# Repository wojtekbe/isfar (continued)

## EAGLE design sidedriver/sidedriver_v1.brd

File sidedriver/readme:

Motor1
M1-PWM -> PA1 -> TIM2_CH2

Tank
M2-PWM -> 

Ledd
SRV1
SRV2
LED-PWM

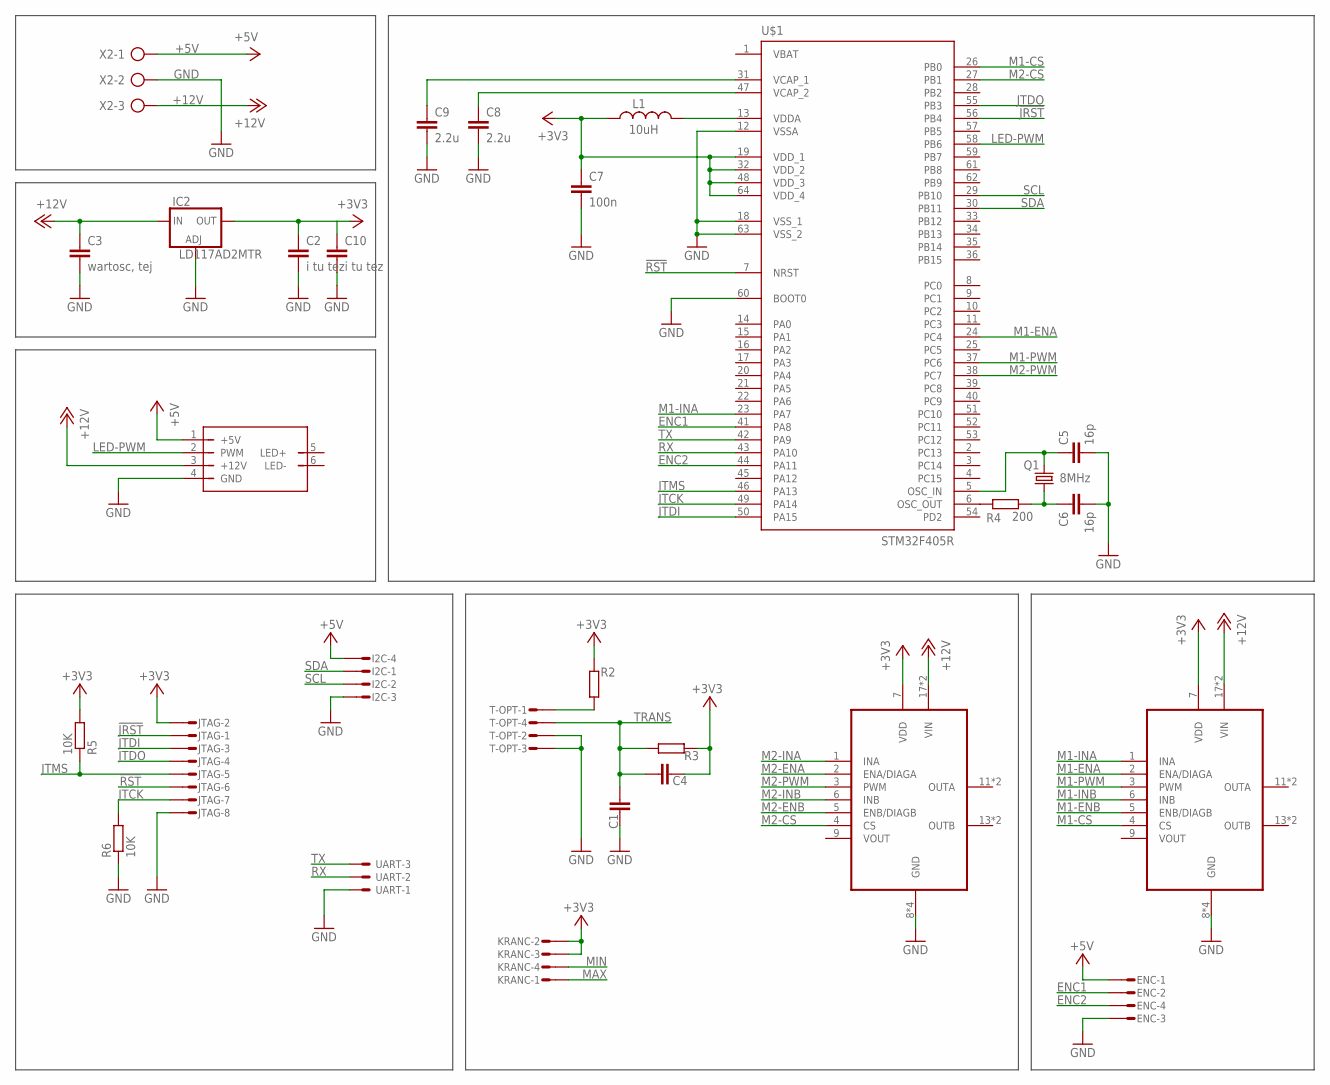
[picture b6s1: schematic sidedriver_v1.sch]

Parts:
C1, C4: C-EUC0603; C0603
C2, C10: i tu tez; C0603
C3: wartosc, tej; C0603
C5, C6: 16p; C0603
C7: 100n; C0603
C8, C9: 2.2u; C0603
ENC: MICROMATCH-4
I2C: MICROMATCH-4
IC2: LD117AD2MTR; D2PACK
JTAG: MICROMATCH-8
KRANC: MICROMATCH-4
L1: 10uH; L0805
Q1: 8MHz; 12SMX
R2, R3: R-EU_R0603; R0603
R4: 200; R0603
R5, R6: 10K; R0603
T-OPT: MICROMATCH-4
U$1: STM32F405R; TQFP64
U$2: LEDD1
U$3, U$4: POLOLU-1451
UART: C-GRID-03-70543; 70543-03
X2: AK500/3

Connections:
!JRST: JTAG.1, U$1.56 (PB4)
!RST: JTAG.6, U$1.7 (NRST)
+3V3: C2.1, C4.1, C7.1, C10.1, IC2.2 (OUT), JTAG.2, KRANC.2, KRANC.3, L1.1, R2.1, R3.1, R5.2, U$1.19 (VDD_1), U$1.32 (VDD_2), U$1.48 (VDD_3), U$1.64 (VDD_4), U$3.7 (VDD), U$4.7 (VDD)
+5V: ENC.1, I2C.4, U$2.1 (+5V), X2.1
+12V: C3.1, IC2.3 (IN), U$2.3 (+12V), U$3.17 (VIN), U$3.18 (VIN), U$4.17 (VIN), U$4.18 (VIN), X2.3
ENC1: ENC.2, U$1.41 (PA8)
ENC2: ENC.4, U$1.44 (PA11)
GND: C1.1, C2.2, C3.2, C5.2, C6.2, C7.2, C8.2, C9.2, C10.2, ENC.3, I2C.3, IC2.1 (ADJ), JTAG.8, R6.1, T-OPT.2, T-OPT.3, U$1.12 (VSSA), U$1.18 (VSS_1), U$1.60 (BOOT0), U$1.63 (VSS_2), U$2.4 (GND), U$3.8 (GND), U$3.10 (GND), U$3.15 (GND), U$3.16 (GND), U$4.8 (GND), U$4.10 (GND), U$4.15 (GND), U$4.16 (GND), UART.1, X2.2
JTCK: JTAG.7, R6.2, U$1.49 (PA14)
JTDI: JTAG.3, U$1.50 (PA15)
JTDO: JTAG.4, U$1.55 (PB3)
JTMS: JTAG.5, R5.1, U$1.46 (PA13)
LED-PWM: U$1.58 (PB6), U$2.2 (PWM)
M1-CS: U$1.26 (PB0), U$4.4 (CS)
M1-ENA: U$1.24 (PC4), U$4.2 (ENA/DIAGA)
M1-ENB: U$4.5 (ENB/DIAGB)
M1-INA: U$1.23 (PA7), U$4.1 (INA)
M1-INB: U$4.6 (INB)
M1-PWM: U$1.37 (PC6), U$4.3 (PWM)
M2-CS: U$1.27 (PB1), U$3.4 (CS)
M2-ENA: U$3.2 (ENA/DIAGA)
M2-ENB: U$3.5 (ENB/DIAGB)
M2-INA: U$3.1 (INA)
M2-INB: U$3.6 (INB)
M2-PWM: U$1.38 (PC7), U$3.3 (PWM)
MAX: KRANC.1
MIN: KRANC.4
unnamed: R2.2, T-OPT.1
unnamed: C6.1, Q1.1, R4.2
unnamed: C5.1, Q1.3 (2), U$1.5 (OSC_IN)
unnamed: L1.2, U$1.13 (VDDA)
unnamed: R4.1, U$1.6 (OSC_OUT)
unnamed: C8.1, U$1.47 (VCAP_2)
unnamed: C9.1, U$1.31 (VCAP_1)
RX: U$1.43 (PA10), UART.2
SCL: I2C.2, U$1.29 (PB10)
SDA: I2C.1, U$1.30 (PB11)
TRANS: C1.2, C4.2, R3.2, T-OPT.4
TX: U$1.42 (PA9), UART.3

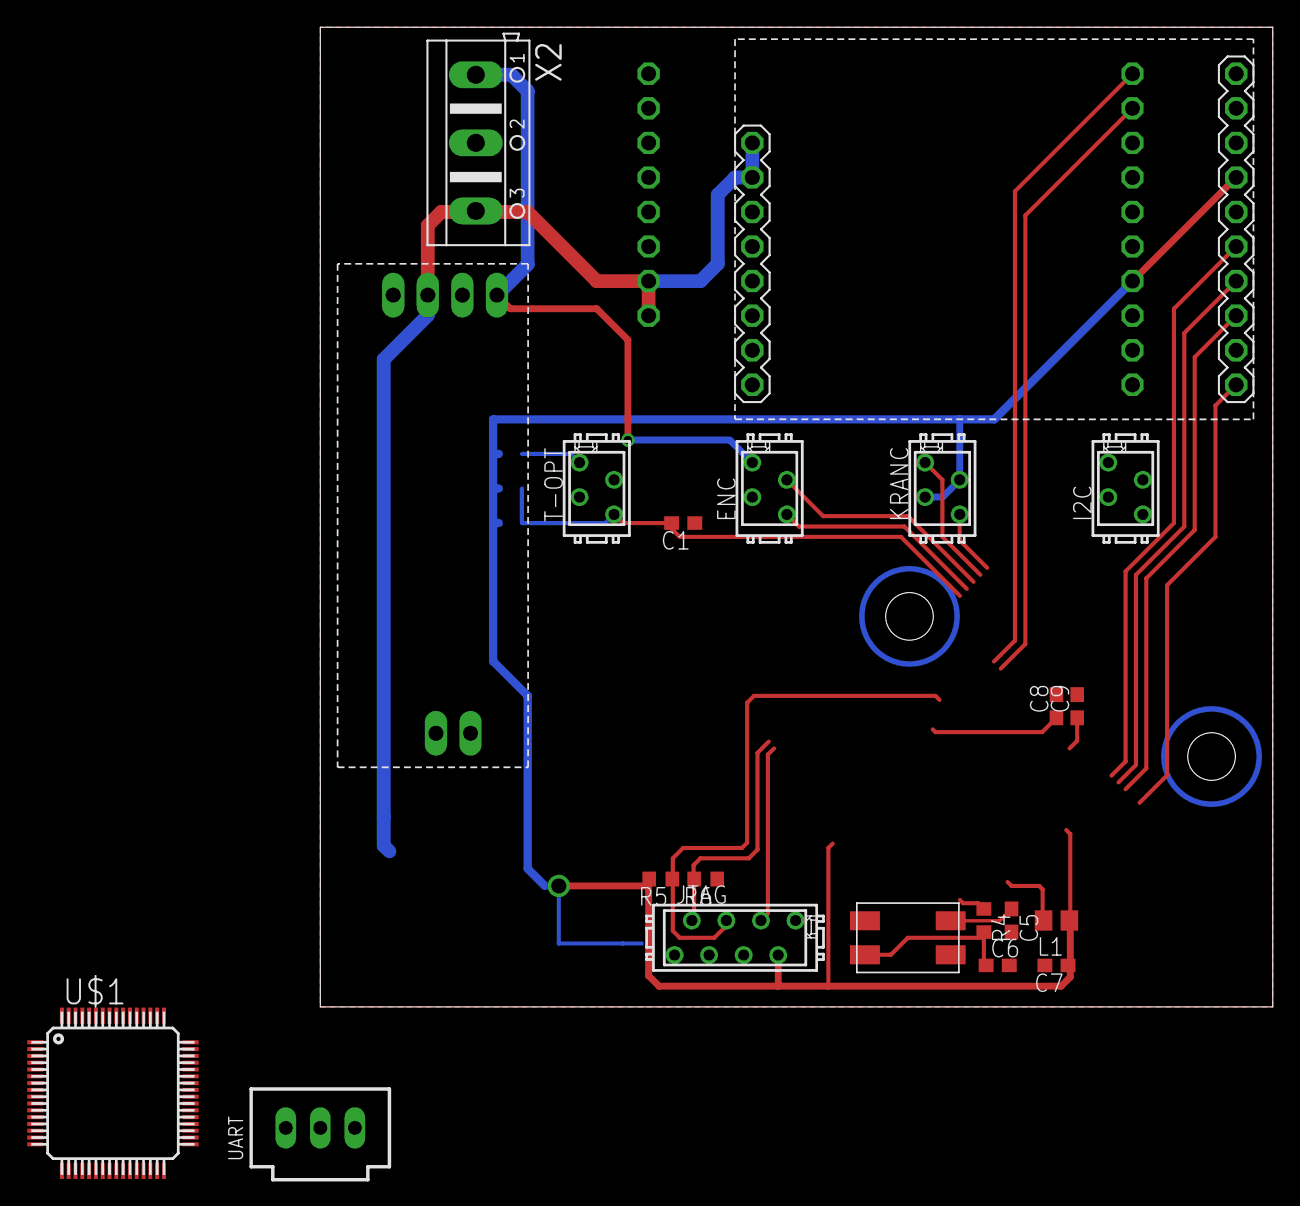
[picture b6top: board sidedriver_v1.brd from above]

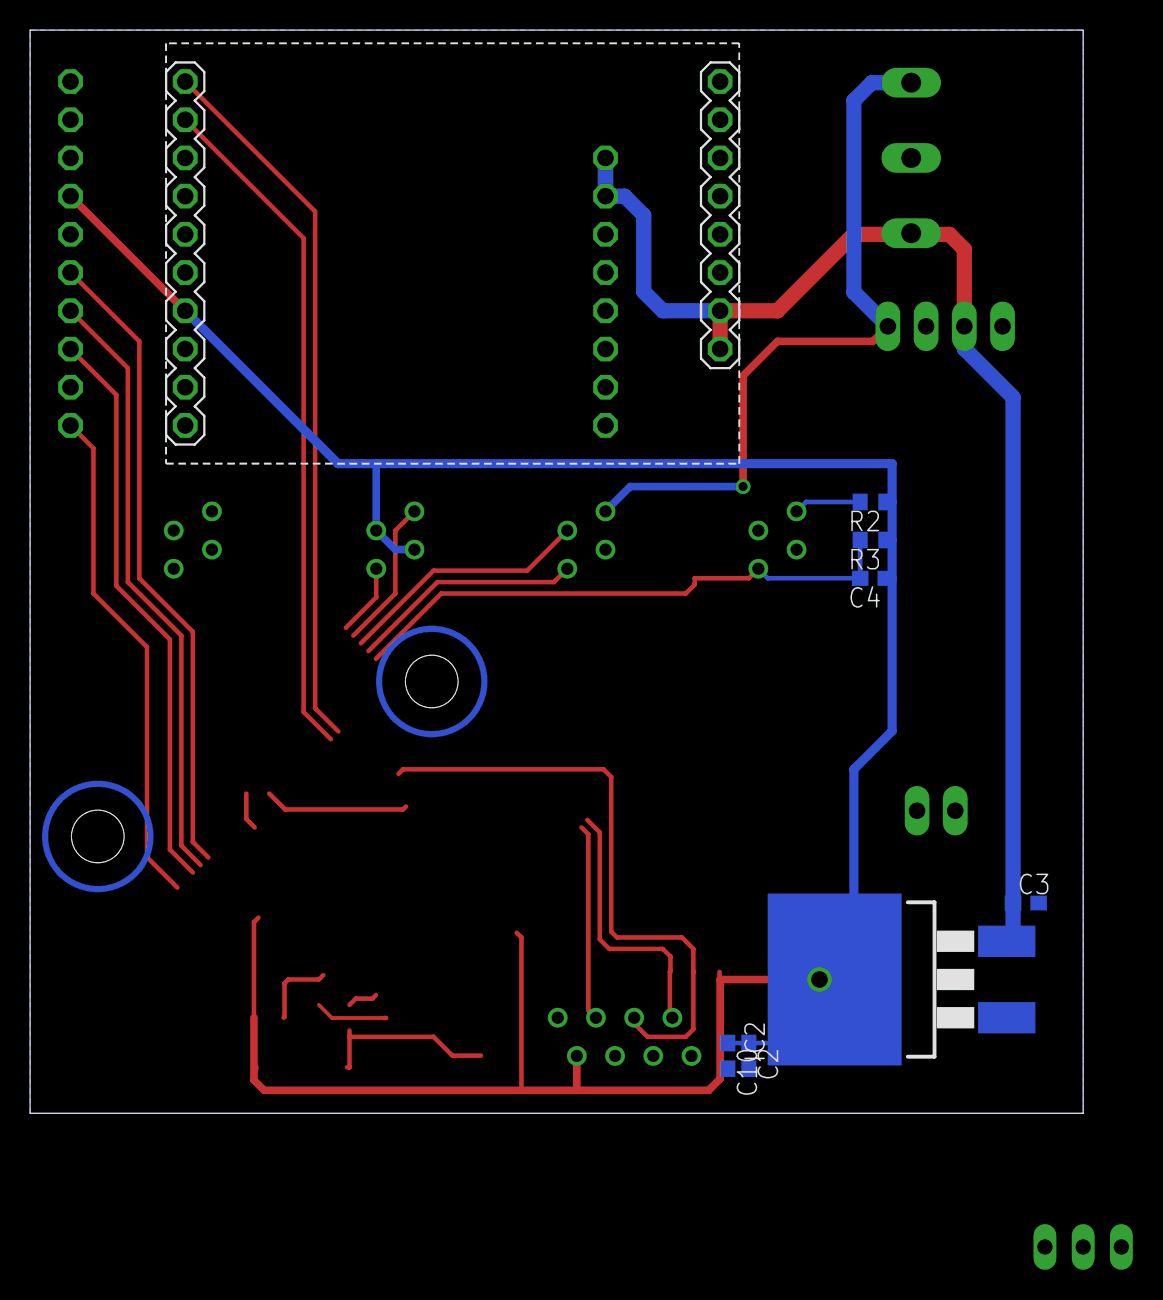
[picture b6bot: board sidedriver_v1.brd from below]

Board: 2 copper layers, 70.0 x 72.0 mm, 29 parts (8 on the bottom side), 31 nets.

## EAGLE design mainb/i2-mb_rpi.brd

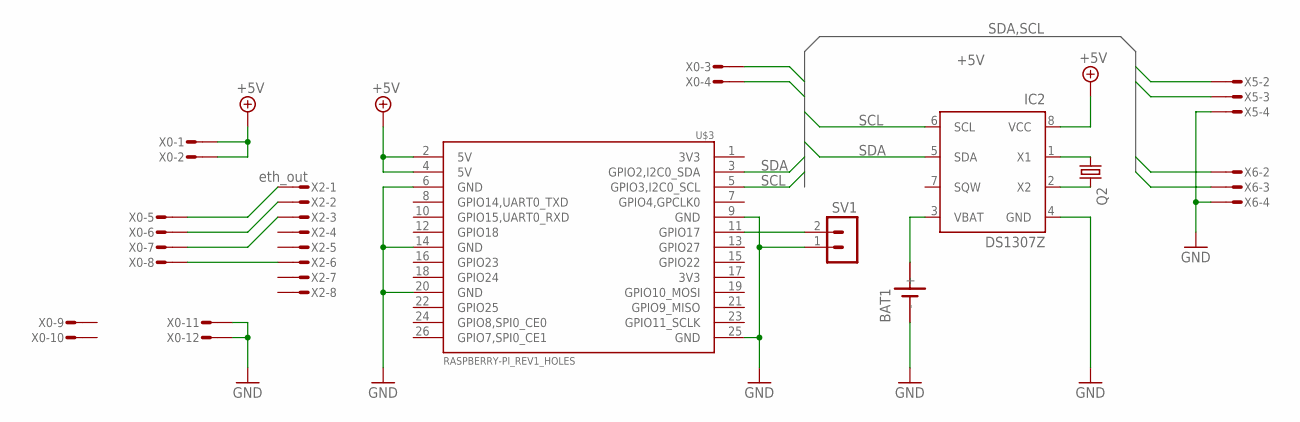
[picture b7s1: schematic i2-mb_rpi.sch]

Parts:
BAT1: SN2032
IC2: DS1307Z; SOIC8
Q2: CRYSTAL; CFPX-217
SV1: MA02-1; MA03-1
U$3: RASPBERRY-PI_REV1_HOLES
X0: MICROMATCH-12
X2: eth_out; MICROMATCH-8
X5: i2c#1; MICROMATCH-4
X6: i2c#2; MICROMATCH-4

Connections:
+5V: IC2.8 (VCC), U$3.2 (5V), U$3.4 (5V), X0.1, X0.2
GND: BAT1.-, IC2.4 (GND), SV1.1, U$3.6 (GND), U$3.9 (GND), U$3.14 (GND), U$3.20 (GND), U$3.25 (GND), X0.11, X0.12, X5.4, X6.4
unnamed: BAT1.+, IC2.3 (VBAT)
unnamed: SV1.2, U$3.11 (GPIO17)
unnamed: X0.5, X2.1
unnamed: X0.6, X2.2
unnamed: X0.7, X2.3
unnamed: IC2.1 (X1), Q2.1
unnamed: X0.8, X2.6
unnamed: IC2.2 (X2), Q2.2
SCL: IC2.6 (SCL), U$3.5 (GPIO3,I2C0_SCL), X0.4, X5.3, X6.3
SDA: IC2.5 (SDA), U$3.3 (GPIO2,I2C0_SDA), X0.3, X5.2, X6.2

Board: 2 copper layers, 9 parts (3 on the bottom side), 12 nets, no tracks yet.

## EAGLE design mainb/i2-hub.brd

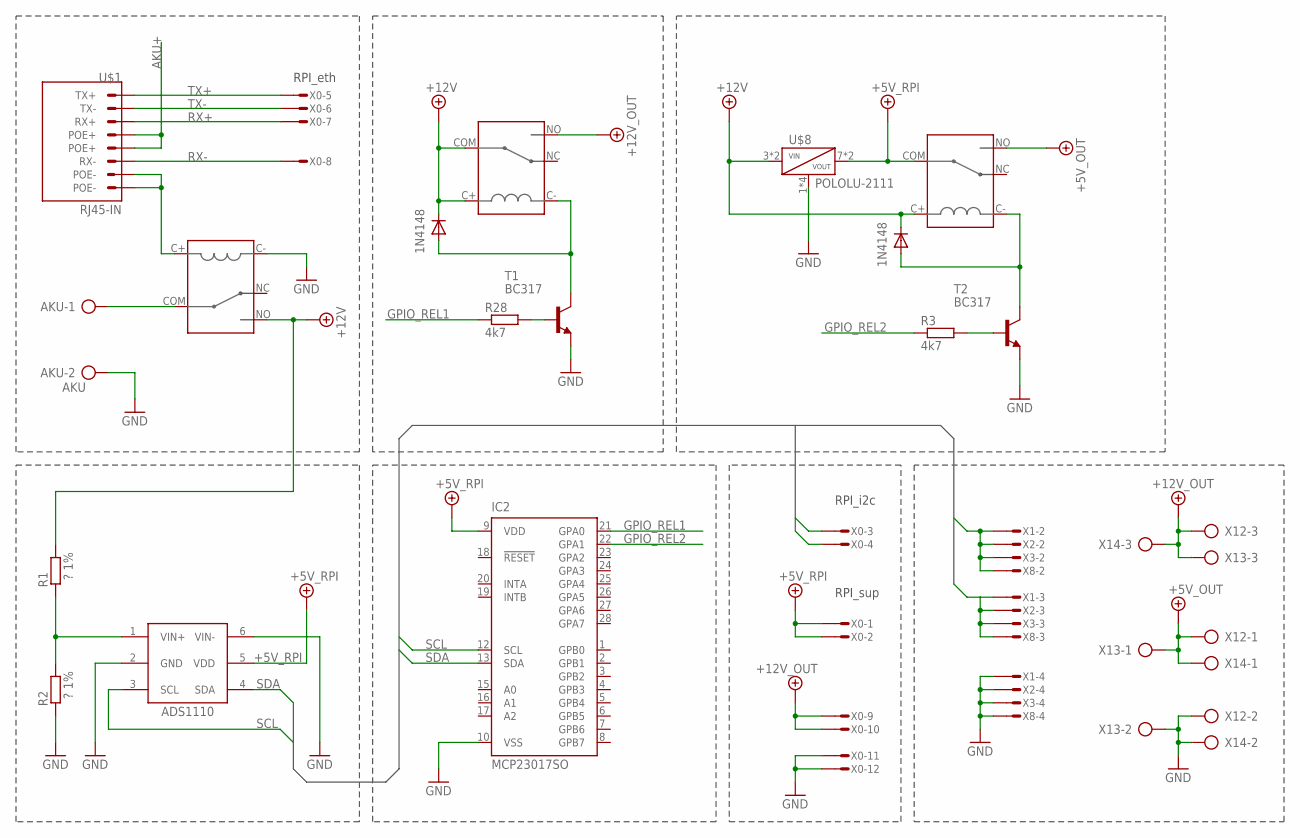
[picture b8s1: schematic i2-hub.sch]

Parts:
AKU: AKU; AK500/2
IC1: ADS1110; SOT-23-6
IC2: MCP23017SO; SO28W
R1, R2: ? 1%; R0603
R3, R28: 4k7; R0603
T1, T2: BC317; SOT23-EBC
U$1: RJ45-IN; 8P8C-TOP
U$3, U$4: 1N4148; D0603
U$5, U$6, U$7: FBR51; PC_RELAY
U$8: POLOLU-2111
X0: MICROMATCH-12
X1, X2, X3, X8: MICROMATCH-4
X12, X13, X14: AK500/3-H

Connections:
+5V: U$5.NO, X12.1, X13.1, X14.1
+5V/1: IC2.9 (VDD)
+5V_RPI: IC1.5 (VDD), U$5.COM, U$8.7 (VOUT), U$8.8 (VOUT), X0.1, X0.2
+12V: R1.1, U$3.2 (C), U$4.2 (C), U$5.C+, U$6.NO, U$7.C+, U$7.COM, U$8.3 (VIN), U$8.4 (VIN), X0.9, X0.10, X12.3, X13.3, X14.3
+12V_OUT: U$7.NO
AKU+: AKU.1, U$1.4 (POE+), U$1.5 (POE+), U$6.COM
GND: AKU.2, IC1.2 (GND), IC1.6 (VIN-), IC2.10 (VSS), R2.2, T1.E, T2.E, U$6.C-, U$8.1 (GND), U$8.2 (GND), U$8.5 (GND), U$8.6 (GND), X0.11, X0.12, X1.4, X2.4, X3.4, X8.4, X12.2, X13.2, X14.2
GPIO_REL1: IC2.21 (GPA0), R28.1
GPIO_REL2: IC2.22 (GPA1), R3.1
unnamed: R3.2, T2.B
unnamed: T2.C, U$3.1 (A), U$5.C-
unnamed: T1.C, U$4.1 (A), U$7.C-
unnamed: R28.2, T1.B
POE-: U$1.7 (POE-), U$1.8 (POE-), U$6.C+
RX+: U$1.1 (RX+), X0.7
RX-: U$1.2 (RX-), X0.8
SCL: IC1.3 (SCL), IC2.12 (SCL), X0.4, X1.3, X2.3, X3.3, X8.3
SDA: IC1.4 (SDA), IC2.13 (SDA), X0.3, X1.2, X2.2, X3.2, X8.2
TX+: U$1.3 (TX+), X0.5
TX-: U$1.6 (TX-), X0.6
V_SENS: IC1.1 (VIN+), R1.2, R2.1

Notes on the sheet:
RPI_eth
RPI_i2c
RPI_sup

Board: 2 copper layers, 24 parts (10 on the bottom side), 19 nets, no tracks yet.

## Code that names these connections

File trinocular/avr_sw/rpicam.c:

//#define F_CPU 1000000UL

#include <avr/io.h>
#include <avr/interrupt.h>

/*
 * LED -> PC0
 * SDA -> PC4
 * SCL -> PC5
 * RXD -> PD0
 * TXD -> PD1
 * SERVO -> OC2 (PB3)
 * PB1 -> Power-LED 1 ctrl
 * PB2 -> Power-LED 2 ctrl
 *
 * OCR2 = 6 - ?? limit
 *
 * Register map:
 * 0x00 status (TODO)
 * 0x01 servo PWM val (in cycles)
 * 0x02 Power-LED 1 (cycles)
 * 0x03 Power-LED 2 (cycles)
*/

#define LED_ON PORTC &= ~0x01
#define LED_OFF PORTC |= 0x01
#define LEDT PORTC ^= 0x01

#define ADDR 0x0A
#define NUM_REGS 4
#define REG_STATUS 0
#define REG_SERVO 1
#define REG_LED1 2
#define REG_LED2 3

uint8_t regs[NUM_REGS] = {0x00, 0x14, 0x80, 0x80};
uint8_t twi_buff[3] = {0xFF, 0xFF, 0xFF};
uint8_t idx = 0;

/* Input/Output */
void init_IO(void)
{
	DDRB = 0xFF;
	DDRD = 0xFF;
	DDRC = 0x01;
	PORTB = 0;
	LED_OFF;
}

/* Timers */
void init_PWM(void)
{
	/* init Timer/Counter1 - powerleds */
	TCCR1A |= _BV(COM1A1) | _BV(COM1B1) | _BV(WGM10);
	TCCR1B |= _BV(WGM12) | _BV(CS10);
	OCR1A = regs[REG_LED1];
	OCR1B = regs[REG_LED2];
	TIMSK |= _BV(TOIE1);

	/* init Timer/Counter2 - servo */
	TCCR2 |= (1 << WGM20) | (1 << WGM21) | (1 << CS22) | (1 << COM21);
	OCR2 = regs[REG_SERVO];
	TIMSK |= _BV(TOIE2);
}

ISR(TIMER1_OVF_vect)
{
	OCR1A = regs[REG_LED1];
	OCR1B = regs[REG_LED2];
}

ISR(TIMER2_OVF_vect)
{
	OCR2 = regs[REG_SERVO];
}

/* UART */
void init_UART(void)
{
	/* Baudrate = 2400 */
	UBRRH = 0x00;
	UBRRL = 0x19;
	UCSRB = (1<<TXEN) | (1<<RXEN);
}

unsigned char us_read()
{
	while (!(UCSRA & (1<<RXC)));
	return UDR;
}

void us_write(char c)
{
	while (!( UCSRA & (1<<UDRE)));
	UDR = c;
}

/* Two-wire interface (I2C) */
void init_TWI(void)
{
	TWAR = (ADDR << 1);
	TWCR |= _BV(TWINT) | _BV(TWEA) | _BV(TWEN) | _BV(TWIE);
}

ISR(TWI_vect)
{
	int i;

	if(TWSR == 0x60) { /* on Write */
		TWCR |= (1 << TWEA);
		idx = 0;
		for(i=0; i<3; i++)
			twi_buff[i] = 0xFF;
	}
	else if(TWSR == 0x80) { /* received a byte */
		twi_buff[idx] = TWDR;
		idx++;
		TWCR |= (1 << TWEA);
	}
	else if(TWSR == 0xA0) { /* on Stop */
		if (twi_buff[0] >= 0 && twi_buff[0] < NUM_REGS) {
			regs[twi_buff[0]] = twi_buff[1];
		}
		/* TODO: else return NACK */
	}
	else if(TWSR == 0xA8) { /* on Read */
		TWDR = 0x00; /* transmit 0x00 */
		TWCR |= (1 << TWEA);
	}
	else if(TWSR == 0xB8) {}
	else if(TWSR == 0xC0) {}
	else if(TWSR == 0xC8) {}

	TWCR |= (1 << TWINT);
}

int main (void)
{
	init_IO();
	init_UART();
	init_PWM();
	init_TWI();
	sei();
	LED_ON;
	us_write(0xEF); /* wite Hello */

	while(1);

	return 0;
}

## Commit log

2013-11-20 libs added, single mainboard (again)
2013-11-20 i2 sidedriver added
2013-11-20 zmieniony ksztalt mainb
2013-11-20 20-11-13 21:08
2013-11-21 21.11.13 23:39
2013-11-22 22.11.13 17:00
2013-11-26 26.11 10:46
2013-11-28 RPi camera board added and library, added servos.lbr
2013-12-03 03-12-13 20:52
2013-12-11 11.12.13 18:50
2013-12-11 11.12.13 18:51
2014-01-26 misc changes
2014-01-28 porzadki w mainb/
2014-01-28 dodano docs/
2014-01-28 rm docs/
2014-01-28 /mainb: 1) pins on relays
2014-01-28 todo file added
2014-01-28 mainb: 3) volt.reg. package dim.
2014-01-28 mainb: 8) leds -> 3V3
2014-01-28 mainb: 7) eth. conn. order
2014-01-28 mainb: 9) battery holder wholes dia
2014-01-28 mainb: 10) RPi UART for debugging
2014-01-28 trinocular/rpicam/ added
2014-02-03 PWM on timer4, and USART2 on Discovery
2014-02-04 sidedriver/readme added
2014-02-04 readmes update
2014-02-04 readmes update ctd...
2014-02-04 fixed USART 0x12 issue
2014-02-10 Signal capturing on TIM3 works
2014-02-11 readme.md modified
2014-02-11 readme.md
2014-02-11 I2C working on Discovery
2014-02-11 rpicam: setup TWI, calibrated servo
2014-02-25 mainb rev. 2 added
2014-02-25 migrating from doscovery to sidedriv. board
2014-02-25 25-02
2014-03-05 trinocular: added app to capture frames from fifo with Opencv
2014-03-08 sidedriver: ledd misc changes
2014-03-11 sidedrv: init funcs for drivers, misc changes
2014-03-11 sidedriver: rm readme.md, pin config in main.c
2014-03-11 rm todo
2014-03-12 sidedriver: i2c improvements in driver-discovery
2014-03-15 sidedriver: improved i2c on discovery
2014-03-15 ignoring *.elf and *.bin
2014-03-15 sidedriver: discovery misc changes
2014-03-15 siderdriver: added i2c support
2014-03-18 some cleanup, ignoring *.o *.hex
2014-03-18 sidedriver: added support for counting encoder ticks, minor improvements
2014-03-19 sidedriver: stopped using STM32F4xx_StdPeriph_Driver, updated Makefile
2014-03-19 sidedriver: misc changes
2014-03-29 siderdriver: initial PID controller implementation
2014-03-29 sidedriver: added support for 2b i2c 'registers'
2014-04-09 sidedriver: PID contr. tests
2014-05-06 sidedriver: some improvements in PID controller
2014-05-07 sidedriver: *.c/*.h split, code cleanup
2014-05-11 sidedriver: PID controller tweaks
2014-05-13 libs/ cleanup
2014-05-13 mainb: mainb_v2 PCB created using kicad
2014-05-13 igoring *-cache.bak
2014-05-14 mainb: mainb_v2 kicad schematic updates
2014-05-14 mainb: kicad sch updates
2014-05-21 sidedriver: fixed a bug in calculating rot. speed (overflow/underflow)
2014-05-28 siderdriver: tankdriver updates, needs some tweaking (transopt.)
2014-05-28 sidedriver: motordriver pid contr. updates
2014-05-28 .gitignore: ignoring kicad_pcb-bak
2014-05-28 some updates in kicad project files, and some cleaning in sidedriver files
2014-05-28 README updates
2014-06-04 sidedriver: resolved transoptor issue
2014-06-07 libs moved somewhere else
2014-06-08 sidedriver: added pinmux.md file
2014-06-08 sidedriver: pinmux.md updateswq
2014-06-08 sidedriver: pinmux.md update
2014-06-08 KiCAD PCB project added
2014-06-08 PCBs: PCB-kicad splitted
2014-06-10 sidedriver: kicad pcb updates
2014-06-10 sidedriver: pid merged to motordriver
2014-06-10 sidedriver: PID tuning
2014-06-10 mainb: added tag for rev1, and provided updates
2014-06-10 sidedriver: Eagle pcb files ranamed
2014-08-05 .gitignore
2014-08-13 sidedriver: added ADC in external port
2014-08-13 sidedriver: pinmux.md updates
2014-08-13 sidedriver: PCB todo file added
2014-08-19 siderdriver: added miliseconds measurement
2014-08-19 sidedriver: ADC calibrated to use with scale
2014-10-07 rpicam: rev2 PCB added
2014-10-21 ledd: added some TODO comments to ledd1.sch
2014-11-03 sidedriver: PCB rev.2 created
2014-11-03 sidedriver: PCB rev.2 updates
2014-12-12 rpicam: updated firmware to work with new PCB
2014-12-16 sidedriver: motordriver for rev.2
2014-12-16 siderdriver: tankdriver for rev.2 in progress...
2015-03-15 rpicam: a script for finding chessboard corners added
2015-04-08 sidedriver: 'make r' doesn't reset the board (compatible with stlink 79b413)
2015-04-08 sidedriver: fix compilation error in tankdriver.c
2015-04-14 sidedriver: warnings, white spaces etc.
2015-04-21 readme update, rst migration
2015-05-19 sidedriver: transopt. -> TIM9_CH2 (not tested)
2015-06-16 sidedriver: tankdriver transoptor to TIM9 work in progress
2015-06-23 sidedriver: debug LED on PA12 support
2015-06-23 sidedriver: toggling debug LED with LEDT()
2015-06-23 sidedriver: tankdriver, isr on TIM9 (transoptor)
2015-07-07 sidedriver: tank resetting procedure
2015-07-17 mainb: initial motor control (mctrl) and tank control (tctrl) scripts
2015-08-11 sidedriver: removed all debug prints
2015-08-11 mainb: scripts moved to proper dir
2015-10-13 sidedriver: turning on tankdriver by default
2015-10-13 mainb: update control scripts
2015-10-29 mainb: adds control client/server scripts
2015-11-03 mainb: ctrl_client: gamepad support
2015-12-03 sidedriver: add delay in td_reset(), change driving speed (PWM)
2015-12-10 sidedriver: tankdriver: td_reset() fix
2015-12-12 sidedriver: tankdriver: MIN/MAX logic
2015-12-12 sidedriver: tankdriver: tank speed set to 75/100
2015-12-12 sidedriver: doscovery: red LED turns on when in HardFault
2015-12-13 sidedriver: discovery: printf() is now from tinyprintf
2015-12-17 mainb: scripts: video server (raspivid+nc) and client (nc+mplayer)
2016-01-26 mainb: updated ctrl scripts, hflipped the video
2016-03-09 mainb: script for switching dhcp to client mode
2016-03-12 sidedriver: printf() bug: debug() uses tinyprintf
2016-03-13 siderdriver: all registers to regs.h
2016-03-13 siderdriver: PID: setting Kp, Ki, Kd via I2C
2016-03-15 sidedriver: PID deadzone
2016-03-17 sidedriver: PID: default Kp = 2/10
2016-07-08 trinocular: rpicam hw revisions in single files
2016-07-08 trinocular: dir reorganized
2016-07-08 trinocular: PCB rev.3 - wip
2016-07-21 trinocular: PCB v3 - wip
2016-08-11 trinocular: rpicam_v3 + gerbers
2017-01-20 README.rst added
2017-01-27 rpicam: avr: code reformat, Timer1 support (LEDs)
2017-04-28 readme: Add board images
